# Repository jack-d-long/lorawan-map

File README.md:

# LoRaWAN Tracker
*Modified Spring 2025 by Jack Long, Charlie Hart, Aleira Sanchez, Chloe Teig for MAE 4220: IoT, Cornell University*

*Originally by Alex Coy, ECE 4950 TA for Spring 2021*

A one‑stop repository for everything you need to build, deploy, and visualize data from our GPS LoRaWAN tracker:

- **Map App** (`map‑app/`)  
  A lightweight web application for ingesting the raw `.txt` logs off the tracker’s onboard SD card and rendering an interactive, real‑time map of your device’s journey.

- **Tracker Hardware** (`tracker‑hardware/`)  
  - **Shell** (`tracker‑hardware/shell_CAD/`)  
    Fully parametric OpenSCAD/STEP files and detailed drawings for 3D‑printing or CNC fabrication of the tracker enclosure.  
  - **Firmware** (`tracker‑hardware/firmware/`)  
    PlatformIO‑compatible C/C++ code for the microcontroller: SD‑card logger, GNSS reader, LoRaWAN uplink, and low‑power sleep modes with GUI.
  - **Purple Board** (`tracker‑hardware/firmware/`)
    KiCAD-compatible files for manufacture and assembly of the EERL 'Purple Board' PCB by Alex Coy, current as of May 2025. 
---

## Repository Structure

```plaintext
lorawan-map/
├── map-app/                   # Web application
│   ├── connectivity_app.py    # Streamlit entrypoint
│   ├── requirements.txt       # Python dependencies
│   ├── templates/             # HTML templates
│
├── tracker-hardware/          
│   ├── shell_CAD/                   # OpenSCAD & STEP enclosure files
│   ├── purple_board/                # EERL purple board docs
│   └── firmware/              
│       ├── feather_sd_sam-m8q-/     # C/C++ source with all proprietary headers
│
├── .gitignore                 
└── README.md                  # ← you are here

```

## The LoRaWAN Tracker 

###  Features

- **Scan and Record LoRaWAN connectivity** Either store data onboard the SD or pull from The Things Network for custom database integration
- **Battery‑aware operation**: real‑time voltage monitoring and on‑screen battery bar  
- **Dual scan modes** (“Drive” vs “Walk”) with adaptive transmit intervals (15 s vs 60 s)  
- **Non‑blocking UI controls**: five‑button D‑pad menu navigation with hardware‑debounced inputs  
- **Persistent storage**: 32 kB FRAM for network session state (optional) + SD card for full JSON logging  
- **Plug‑and‑play web front‑end**: drag‑and‑drop `.txt` logs to visualize GPS tracks, timestamps and sensor graphs  

---

###  Hardware Requirements

- **Microcontroller**: Adafruit Feather M0 LoRa ([RFM95, 915 MHz](https://www.adafruit.com/product/3178))  
- **"Purple Board"**: EERL PCB (source included)
- **Display**: [SH1106 128×64 I²C OLED](https://www.aliexpress.us/item/3256806846801359.html?src=google&pdp_npi=4%40dis%21USD%216.32%213.11%21%21%21%21%21%40%2112000039161970280%21ppc%21%21%21&src=google&albch=shopping&acnt=708-803-3821&isdl=y&slnk=&plac=&mtctp=&albbt=Google_7_shopping&aff_platform=google&aff_short_key=UneMJZVf&gclsrc=aw.ds&albagn=888888&ds_e_adid=&ds_e_matchtype=&ds_e_device=c&ds_e_network=x&ds_e_product_group_id=&ds_e_product_id=en3256806846801359&ds_e_product_merchant_id=5388525816&ds_e_product_country=US&ds_e_product_language=en&ds_e_product_channel=online&ds_e_product_store_id=&ds_url_v=2&albcp=20123152476&albag=&isSmbAutoCall=false&needSmbHouyi=false&gad_source=1&gad_campaignid=20127768206&gbraid=0AAAAAD6I-hE0CYYoGWDb82JdLxJdh6HZj&gclid=Cj0KCQjwrPHABhCIARIsAFW2XBMoG-_e8-ALzsrb52M93WnFTvrb6fn9T6qEIRYuo83KG5EKEKTS-N8aAq3UEALw_wcB&gatewayAdapt=glo2usa)
- **GPS**: u‑blox SAM‑M8Q module ([Sparkfun breakout](https://www.sparkfun.com/sparkfun-gps-breakout-chip-antenna-sam-m8q-qwiic.html))  
- **Storage**: [MicroSD card breakout](https://www.amazon.com/UMLIFE-Interface-Conversion-Compatible-Raspberry/dp/B0989SM146) with Micro SD (>8GB) + MCCI Catena cFram32k FRAM (optional)
- **Controls**: [PCA9554 I²C D‑Pad](https://www.sparkfun.com/sparkfun-qwiic-directional-pad.html) + [12mm latching pushbutton](https://www.amazon.com/Gebildet-Latcting-Lockable-Trumpet-Doorbell/dp/B07YDCJFZJ?source=ps-sl-shoppingads-lpcontext&ref_=fplfs&psc=1&smid=A86AD06S3OMVQ&gQT=0)
- **Power**: 3.7 V 1S/3C LiPo battery (800-1000 mAh)   
- **Enclosure**: 3D‑printed shell (source included)  

---

### Software Requirements

- **Arduino IDE**   
- Libraries:  
  - `Arduino_LoRaWAN_ttn` + `lmic`  
  - `Adafruit GFX` & `Adafruit SH110X`  
  - `SparkFun u‑blox GNSS` & `TinyGPS`  
  - `SparkFun I2C Expander`  
  - `MCCI Catena FrAM`  
- **Node.js** (v14+) & **npm** for the web app  
- Web dependencies: `express`, `react`, `leaflet`, `chart.js`

---

## Usage

**1. Clone the repo**
```
git clone https://github.com/jack-d-long/lorawan-map.git
cd lorawan-map
```

**2. Build the tracker**
- Purchase components, print shell, assemble.
  - Printed with PLA at 0.2 mm layer height, tree supports
- Flash firmware with Arduino IDE

**3. Use the tracker**
- Collect data on LoRaWAN connectivity in your local area

**4. Set up the map app**
- Install dependencies

```
pip install --upgrade pip
pip install \
  streamlit \
  pandas \
  pydeck \
  jsonschema  # optional: validate JSON if you extend
```

**5. Read your stored data card with the map app**
- Read your tracker's SD storage with your computer
- Run the app

```
streamlit run connectivity_app.py
```
- Drag and drop the `.txt` file from the SD into the app
- Read your map!

**6. Read your data on the cloud via TTN**

- Set up TTN by following Labs 3, 4, 5, and 6 of [this tutorial](https://pages.github.coecis.cornell.edu/LPWAN-Training/training-labs/lab3), or equivalent
- Pipe your data via MQTT to the database of your choice for live retrieval

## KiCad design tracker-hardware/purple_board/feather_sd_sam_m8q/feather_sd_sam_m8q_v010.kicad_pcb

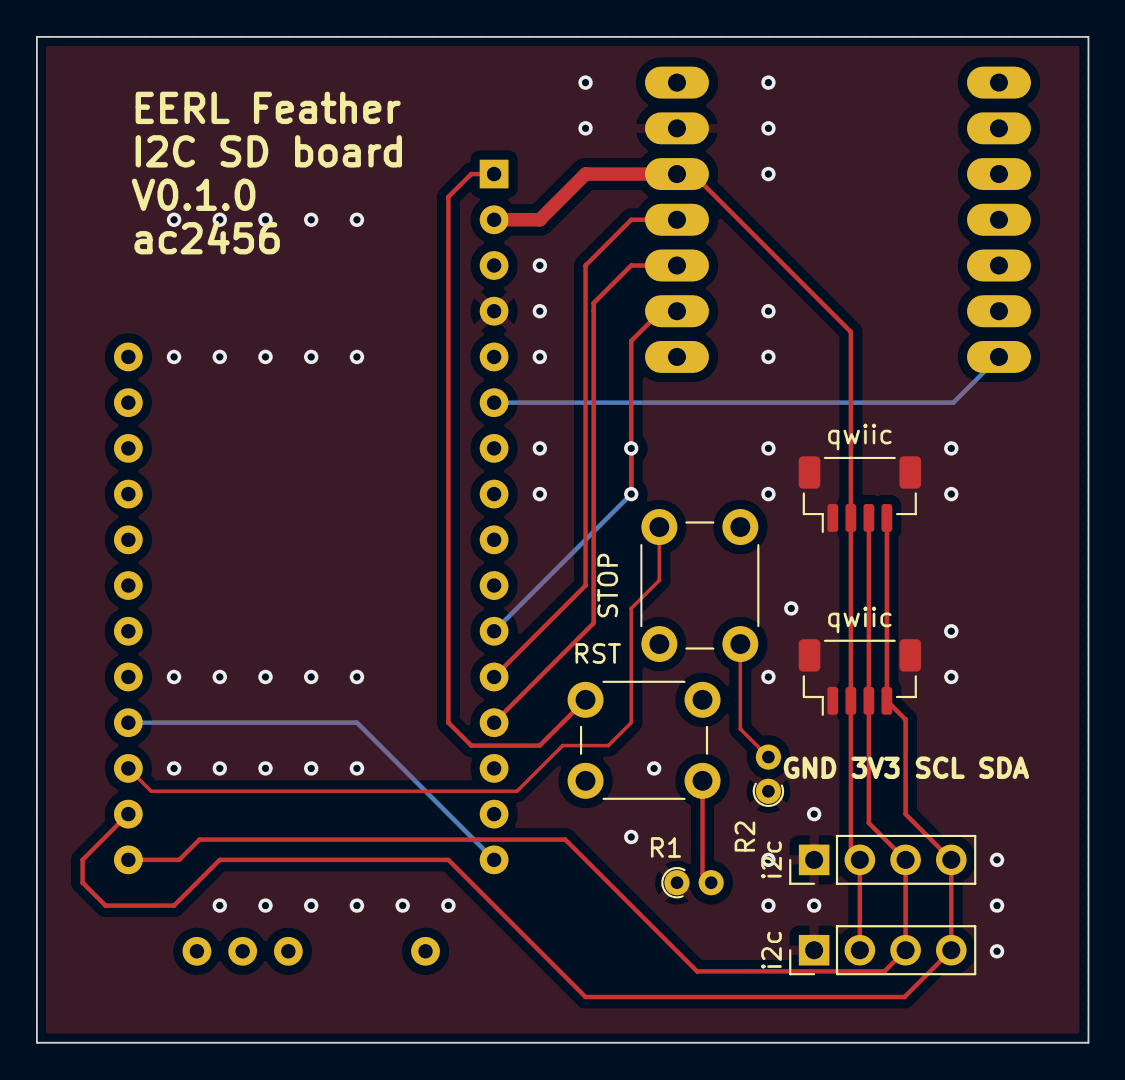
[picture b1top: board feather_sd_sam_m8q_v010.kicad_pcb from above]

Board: 2 copper layers, 58.4 x 55.9 mm, 9 parts (1 on the bottom side), 7 nets.

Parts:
A1: Adafruit_Feather_M0_RFM9x_LoRa_Radio; Adafruit_Feather_M0_RFM
R1, R2: R_Axial_DIN0204_L3.6mm_D1.6mm_P1.90mm_Vertical
RST: SW_PUSH_6mm
STOP: SW_PUSH_6mm
i2c, i2c#2: PinHeader_1x04_P2.54mm_Vertical
qwiic: JST_SH_BM04B-SRSS-TB_1x04-1MP_P1.00mm_Vertical
qwiic#2: JST_SH_BM04B-SRSS-TB_1x04-1MP_P1.00mm_Vertical

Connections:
/SCL: A1.18 (SCL/D21), i2c.4, i2c#2.4, qwiic.4, qwiic#2.4
/SDA: A1.17 (SDA/D20), i2c.3, i2c#2.3, qwiic.3, qwiic#2.3
/VDD3v: A1.2 (3V3), i2c.2, i2c#2.2, qwiic.2, qwiic#2.2
/VSS: A1.4 (GND), R1.1, R2.1, i2c.1, i2c#2.1, qwiic.1, qwiic.MP, qwiic#2.1, qwiic#2.MP
/jp6_1: A1.16 (DIO1), A1.20 (D6)
RST: A1.1 (~RESET), RST.1
stop_button: A1.19 (D5), STOP.1

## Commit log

2025-05-09 change connectivity criteria to reflect firmware
2025-05-09 reorg, add hardware/firmware
2025-05-09 reorg CAD, add purple board
2025-05-09 modified README
2025-05-09 readme
2025-05-11 update map app to reflect firmware save format
2025-05-11 modify README
2025-05-11 add lat/long to map app tooltip
